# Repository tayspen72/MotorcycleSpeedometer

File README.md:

# `Motorcycle Speedometer`

The motorcycle speedometer project is meant to be a full functional replacement for the speedometer and instrument panel for the 2001 Sukuki VL1500 Intruder speedometer assembly. For this model, the assembly includes:
* Speedometer
* Odometer and Trip Meter
* High-beam indicator
* Fuel Level
* Left/Right Turn indicator
* Neutral indicator
* Oil pressure indicator

Because of other connections and available info, the project also includes:
* Battery voltage
* Speedometer assembly temperature
* Run time / clock
* Bluetooth connection for calibration and time adjustment

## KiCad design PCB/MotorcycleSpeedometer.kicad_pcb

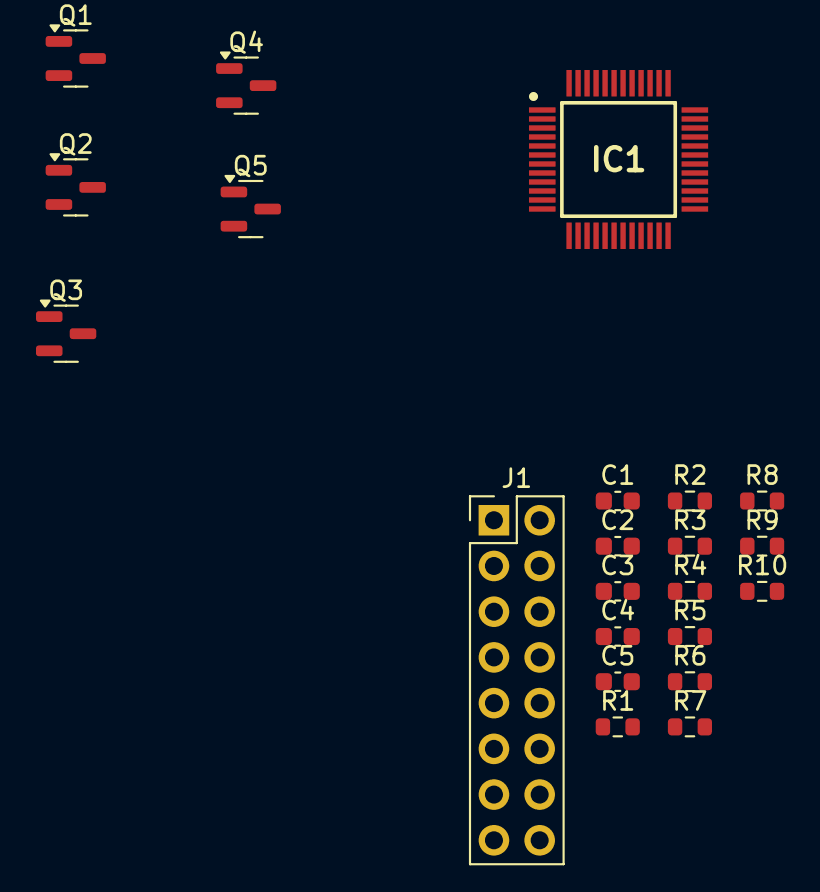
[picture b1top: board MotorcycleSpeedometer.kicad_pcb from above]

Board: 2 copper layers, 22 parts (0 on the bottom side), 12 nets, no tracks yet.

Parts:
C1: 10uF; C_0603_1608Metric
C2, C3, C4, C5: 100nF; C_0603_1608Metric
IC1: STM32U083CCT6; QFP50P900X900X160-48N
J1: Conn_02x08_Odd_Even; PinHeader_2x08_P2.54mm_Vertical
Q1, Q2, Q3: 2N7002; SOT-23
Q4, Q5: AO3401A; SOT-23
R1, R2, R3, R4, R5, R6, R7, R8, R9, R10: R; R_0603_1608Metric

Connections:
+3.3V: C1.1, C2.1, C3.1, C4.1, C5.1, IC1.1 (VBAT), IC1.9 (VDDA/VREF+), IC1.24 (VDD_1), IC1.36 (VDDUSB), IC1.48 (VDD_2), Q1.3 (D), Q2.3 (D), Q3.3 (D)
+BATT: J1.1, Q4.3 (D), Q5.3 (D), R9.1, R10.1
/BEAM_EXT: J1.7, R1.1
/LTURN_EXT: J1.5, R3.1
/OIL_EXT: J1.11, R8.1
/RTURN_EXT: J1.3, R5.1
GND: C1.2, C2.2, C3.2, C4.2, C5.2, IC1.8 (VSSA/VREF-), IC1.23 (VSS_1), IC1.35 (VSS_2), IC1.47 (VSS_3), J1.6, J1.15, Q1.2 (S), Q2.2 (S), Q3.2 (S), Q4.2 (S), Q5.2 (S), R2.2, R4.2, R6.2
unnamed: Q1.1 (G), R1.2, R2.1
unnamed: Q2.1 (G), R3.2, R4.1
unnamed: Q3.1 (G), R5.2, R6.1
unnamed: Q4.1 (G), R7.2, R9.2
unnamed: Q5.1 (G), R8.2, R10.2

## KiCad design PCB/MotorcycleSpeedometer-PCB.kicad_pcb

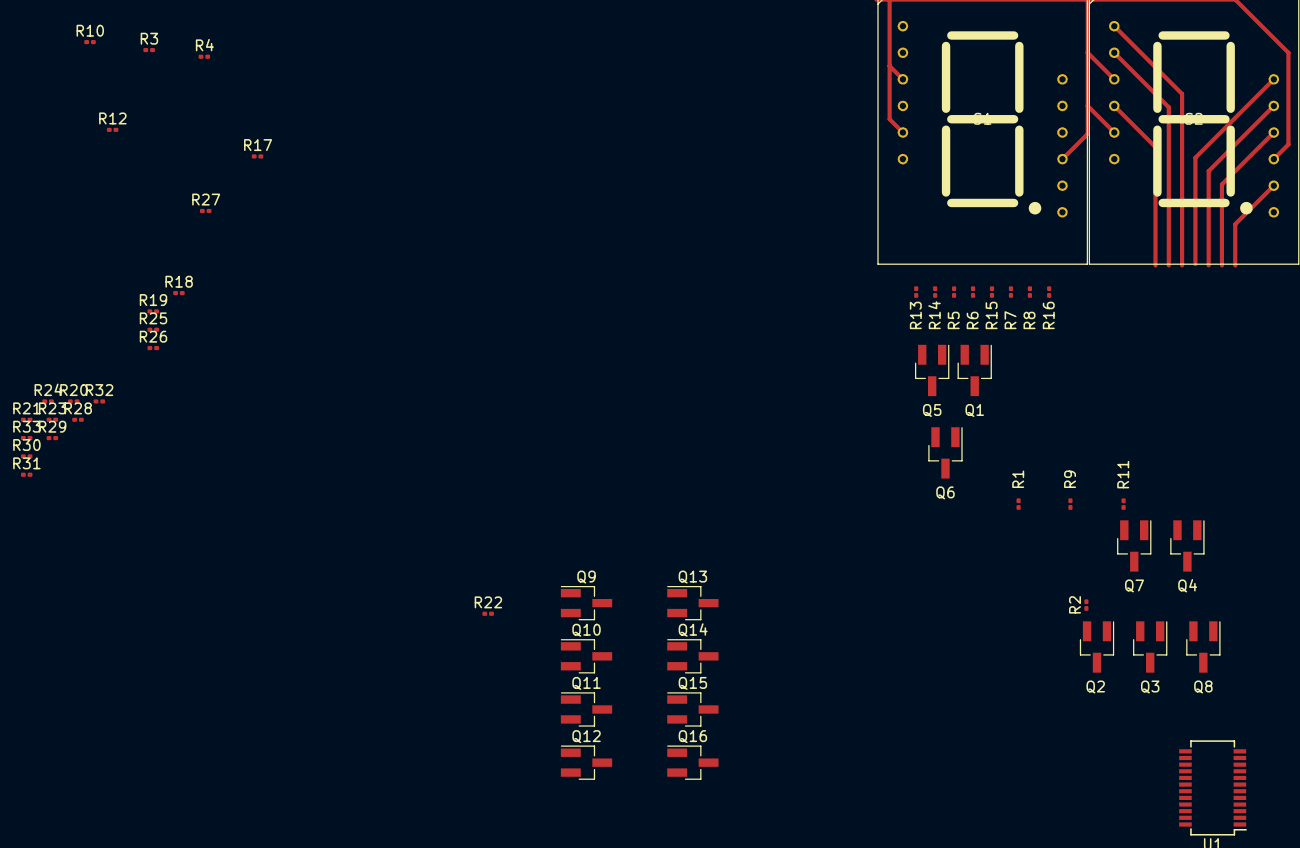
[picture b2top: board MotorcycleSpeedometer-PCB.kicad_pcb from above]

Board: 2 copper layers, 52 parts (0 on the bottom side), 47 nets.

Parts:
Q1, Q3, Q4, Q5, Q6, Q7, Q8, Q9, Q10, Q11, Q12, Q13, Q14, Q15, Q16: Q_NMOS_DGS; SOT-23_Handsoldering
Q2: ee; SOT-23_Handsoldering
R1: e; R_0201_0603Metric
R2, R3, R4, R9, R10, R11, R12, R17, R18, R19, R20, R25, R26, R27, R28: 10k; R_0201_0603Metric
R5, R6, R7, R8, R13, R14, R15, R16, R21, R22, R23, R24, R29, R30, R31, R32: 100R; R_0201_0603Metric
R33: 20k; R_0201_0603Metric
S1, S2: CDSA80W2WB-1DP
U1: TLC59281DBQR; SSOP-24_3.9x8.7mm_P0.635mm

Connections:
/D1SA: R5.1, S1.1
/D1SA_G: Q1.2, R1.1, U1.5
/D1SB: R6.1, S1.12
/D1SB_G: Q2.2, R2.1, U1.6
/D1SC: R7.1, S1.10
/D1SC_G: Q3.2, R3.1, U1.7
/D1SD: R8.1, S1.8
/D1SD_G: Q4.2, R4.1, U1.8
/D1SE: R13.1, S1.4
/D1SE_G: Q5.2, R9.1, U1.9
/D1SF: R14.1, S1.2
/D1SF_G: Q6.2, R10.1, U1.10, U1.11
/D1SG: R15.1, S1.11
/D1SG_G: Q7.2, R11.1
/D1SRDP: R16.1, S1.7
/D1SRDP_G: Q8.2, R12.1, U1.12
/D2SA: R21.1, S2.1
/D2SA_G: Q9.2, R17.1, U1.13
/D2SB: R22.1, S2.12
/D2SB_G: Q10.2, R18.1, U1.14
/D2SE: R23.1, R24.1, R29.1, S2.4
/D2SE_G: Q11.2, Q12.2, Q13.2, R19.1, R20.1, R25.1, U1.17
/D2SF: R30.1, S2.2
/D2SF_G: Q14.2, R26.1, U1.18, U1.19
/D2SG: R31.1, S2.11
/D2SG_G: Q15.2, R27.1
/D2SRDP: R32.1, S2.7
/D2SRDP_G: Q16.2, R28.1, U1.20
/VCC5: S1.3, S1.5, S1.9, S2.3, S2.5, S2.9, U1.24
GND: Q1.3, Q2.3, Q3.3, Q4.3, Q5.3, Q6.3, Q7.3, Q8.3, Q9.3, Q10.3, Q11.3, Q12.3, Q13.3, Q14.3, Q15.3, Q16.3, R1.2, R2.2, R3.2, R4.2, R9.2, R10.2, R11.2, R12.2, R17.2, R18.2, R19.2, R20.2, R25.2, R26.2, R27.2, R28.2, R33.2, U1.1, U1.21
unnamed: Q1.1, R5.2
unnamed: Q2.1, R6.2
unnamed: Q3.1, R7.2
unnamed: Q4.1, R8.2
unnamed: Q5.1, R13.2
unnamed: Q6.1, R14.2
unnamed: Q7.1, R15.2
unnamed: Q8.1, R16.2
unnamed: Q9.1, R21.2
unnamed: Q10.1, R22.2
unnamed: Q11.1, R23.2
unnamed: Q12.1, R24.2
unnamed: Q13.1, R29.2
unnamed: Q14.1, R30.2
unnamed: Q15.1, R31.2
unnamed: Q16.1, R32.2
unnamed: R33.1, U1.23

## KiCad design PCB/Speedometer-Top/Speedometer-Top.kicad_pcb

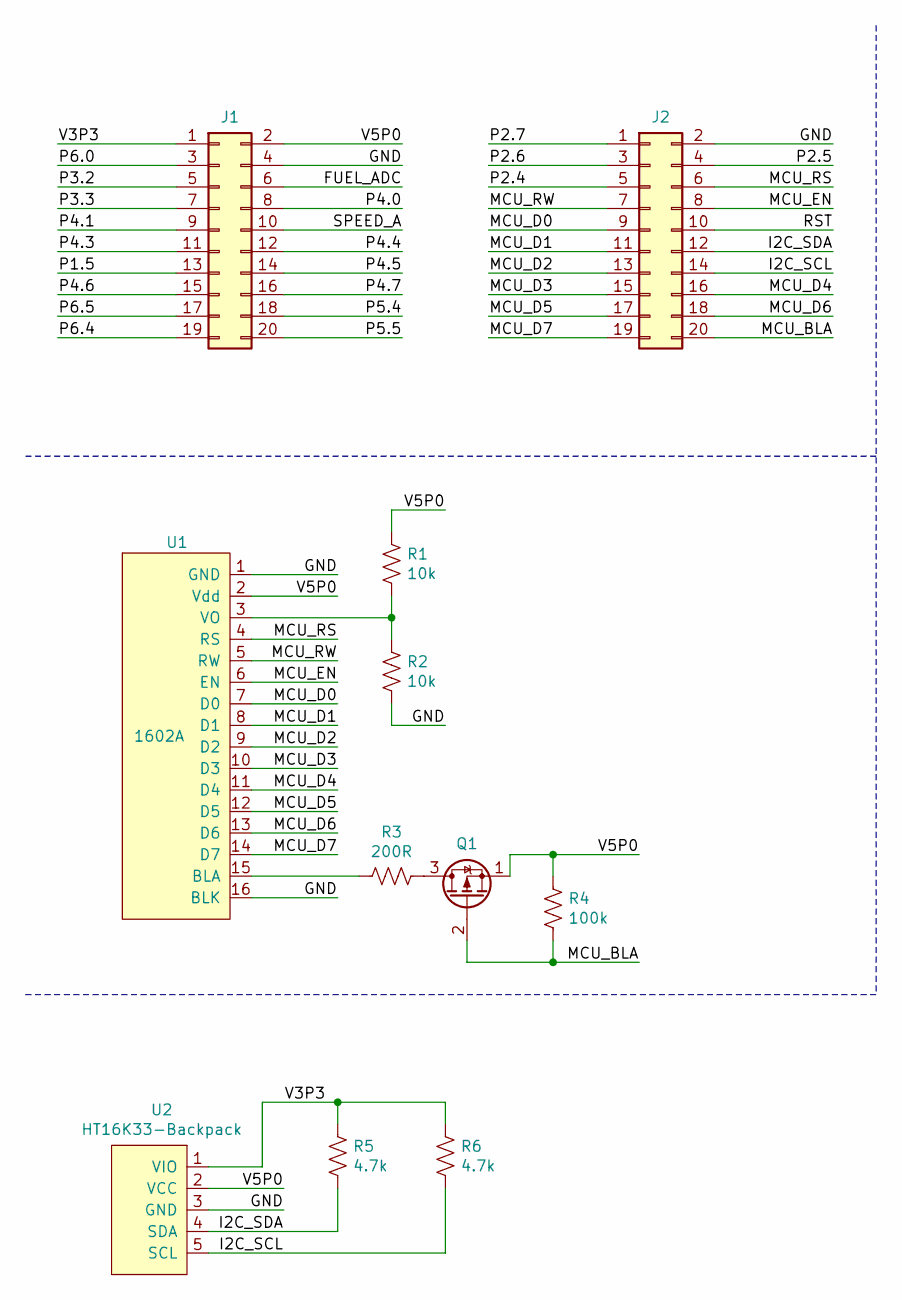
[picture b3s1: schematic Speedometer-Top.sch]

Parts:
J1, J2: Conn_02x10_Odd_Even; PinHeader_2x10_P2.54mm_Vertical
Q1: Q_PMOS_SGD; SOT-23
R1, R2: 10k; R_0603_1608Metric
R3: 200R; R_0603_1608Metric
R4: 100k; R_0603_1608Metric
R5, R6: 4.7k; R_0603_1608Metric
U1: 1602A; PinHeader_1x16_P2.54mm_Vertical
U2: HT16K33-Backpack; PinHeader_1x05_P2.54mm_Vertical

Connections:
/FUEL_ADC: J1.6
/GND: J1.4, J2.2, R2.1, U1.1 (GND), U1.16 (BLK), U2.3 (GND)
/I2C_SCL: J2.14, R6.1, U2.5 (SCL)
/I2C_SDA: J2.12, R5.1, U2.4 (SDA)
/MCU_BLA: J2.20, Q1.2 (G), R4.1
/MCU_D0: J2.9, U1.7 (D0)
/MCU_D1: J2.11, U1.8 (D1)
/MCU_D2: J2.13, U1.9 (D2)
/MCU_D3: J2.15, U1.10 (D3)
/MCU_D4: J2.16, U1.11 (D4)
/MCU_D5: J2.17, U1.12 (D5)
/MCU_D6: J2.18, U1.13 (D6)
/MCU_D7: J2.19, U1.14 (D7)
/MCU_EN: J2.8, U1.6 (EN)
/MCU_RS: J2.6, U1.4 (RS)
/MCU_RW: J2.7, U1.5 (RW)
/P1.5: J1.13
/P2.4: J2.5
/P2.5: J2.4
/P2.6: J2.3
/P2.7: J2.1
/P3.2: J1.5
/P3.3: J1.7
/P4.0: J1.8
/P4.1: J1.9
/P4.3: J1.11
/P4.4: J1.12
/P4.5: J1.14
/P4.6: J1.15
/P4.7: J1.16
/P5.4: J1.18
/P5.5: J1.20
/P6.0: J1.3
/P6.4: J1.19
/P6.5: J1.17
/RST: J2.10
/SPEED_A: J1.10
/V3P3: J1.1, R5.2, R6.2, U2.1 (VIO)
/V5P0: J1.2, Q1.1 (S), R1.2, R4.2, U1.2 (Vdd), U2.2 (VCC)
unnamed: Q1.3 (D), R3.2
unnamed: R1.1, R2.2, U1.3 (VO)
unnamed: R3.1, U1.15 (BLA)

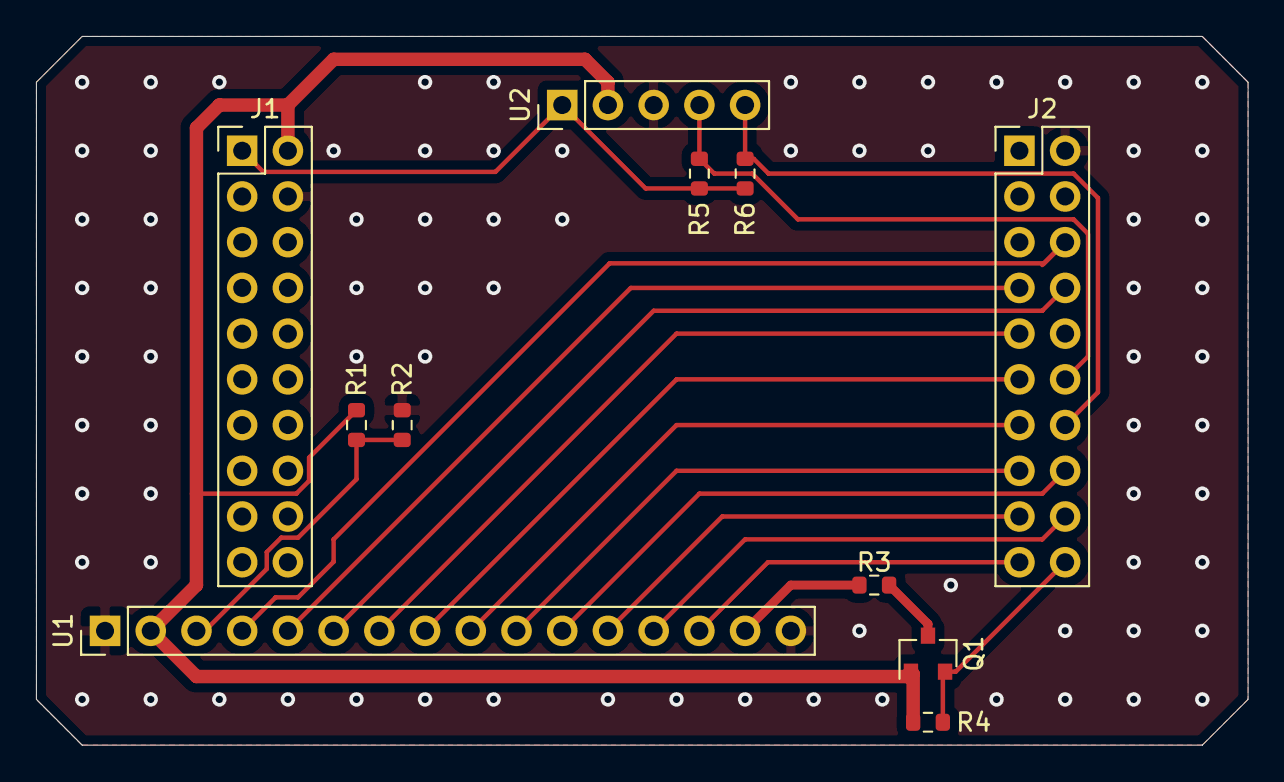
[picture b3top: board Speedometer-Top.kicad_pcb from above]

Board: 2 copper layers, 67.3 x 39.4 mm, 11 parts (0 on the bottom side), 20 nets.

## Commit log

2021-03-16 Begin tracking the C project
2021-03-16 Begin tracking the KiCad PCB project
2021-03-16 Begin tracking the EAGLE PCB project
2021-03-16 Initial rust implementation - needs merge from nrf mcu
2021-03-16 Move readme file to root folder:
2021-03-16 Included .gitignore file
2021-04-27 Moving forward with KiCad only, starting from scratch
2021-04-27 Tracking vscode config
2021-08-16 Update for new file org and projects
2021-09-07 Adding pdf of schematic
2022-06-07 Rebuild and reconfig for the stm32f1 MCU
2022-06-07 remove this - added by mistake
2024-05-28 Migrating to nrf_connect_sdk and new PCB design
2024-05-28 Initial work on control library
2025-04-17 Updated PCB
2025-04-17 merge
2025-05-08 incremental dev
